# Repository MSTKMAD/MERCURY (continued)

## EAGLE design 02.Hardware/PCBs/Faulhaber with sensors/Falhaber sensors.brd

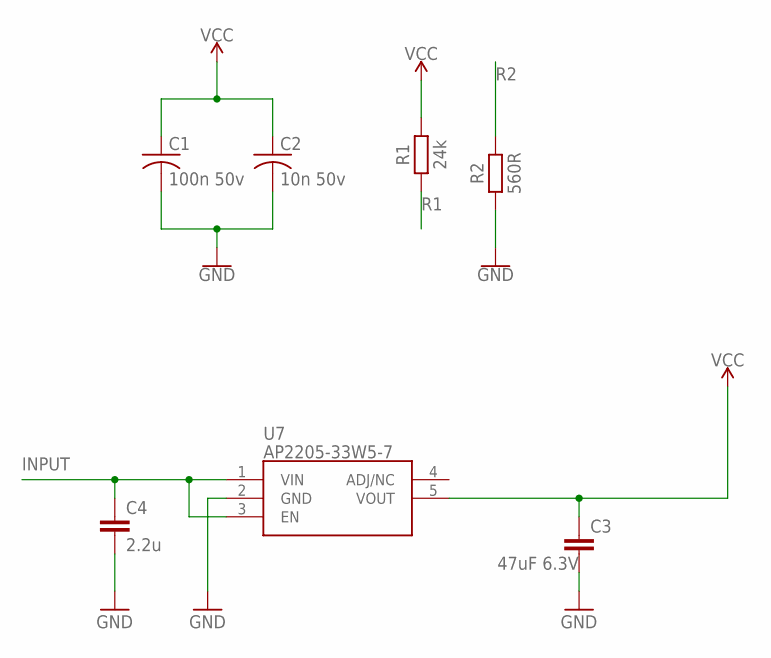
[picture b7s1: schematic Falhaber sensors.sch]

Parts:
C1: 100n 50v; C0805
C2: 10n 50v; C0805
C3: 47uF 6.3V; 0603-CAP
C4: 2.2u; 0603-CAP
R1: 24k; RESC2012X65
R2: 560R; RESC2012X65
U7: AP2205-33W5-7; SOT95P282X145-5N

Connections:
GND: C1.2, C2.2, C3.2, C4.2, R2.1, U7.2 (GND)
INPUT: C4.1, U7.1 (VIN), U7.3 (EN)
R1: R1.1
R2: R2.2
VCC: C1.1, C2.1, C3.1, R1.2, U7.5 (VOUT)

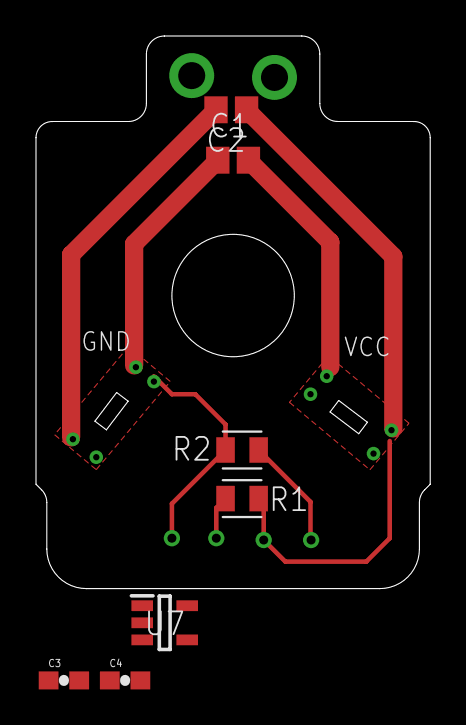
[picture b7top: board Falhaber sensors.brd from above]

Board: 2 copper layers, 21.9 x 30.7 mm, 7 parts (0 on the bottom side), 3 nets.
